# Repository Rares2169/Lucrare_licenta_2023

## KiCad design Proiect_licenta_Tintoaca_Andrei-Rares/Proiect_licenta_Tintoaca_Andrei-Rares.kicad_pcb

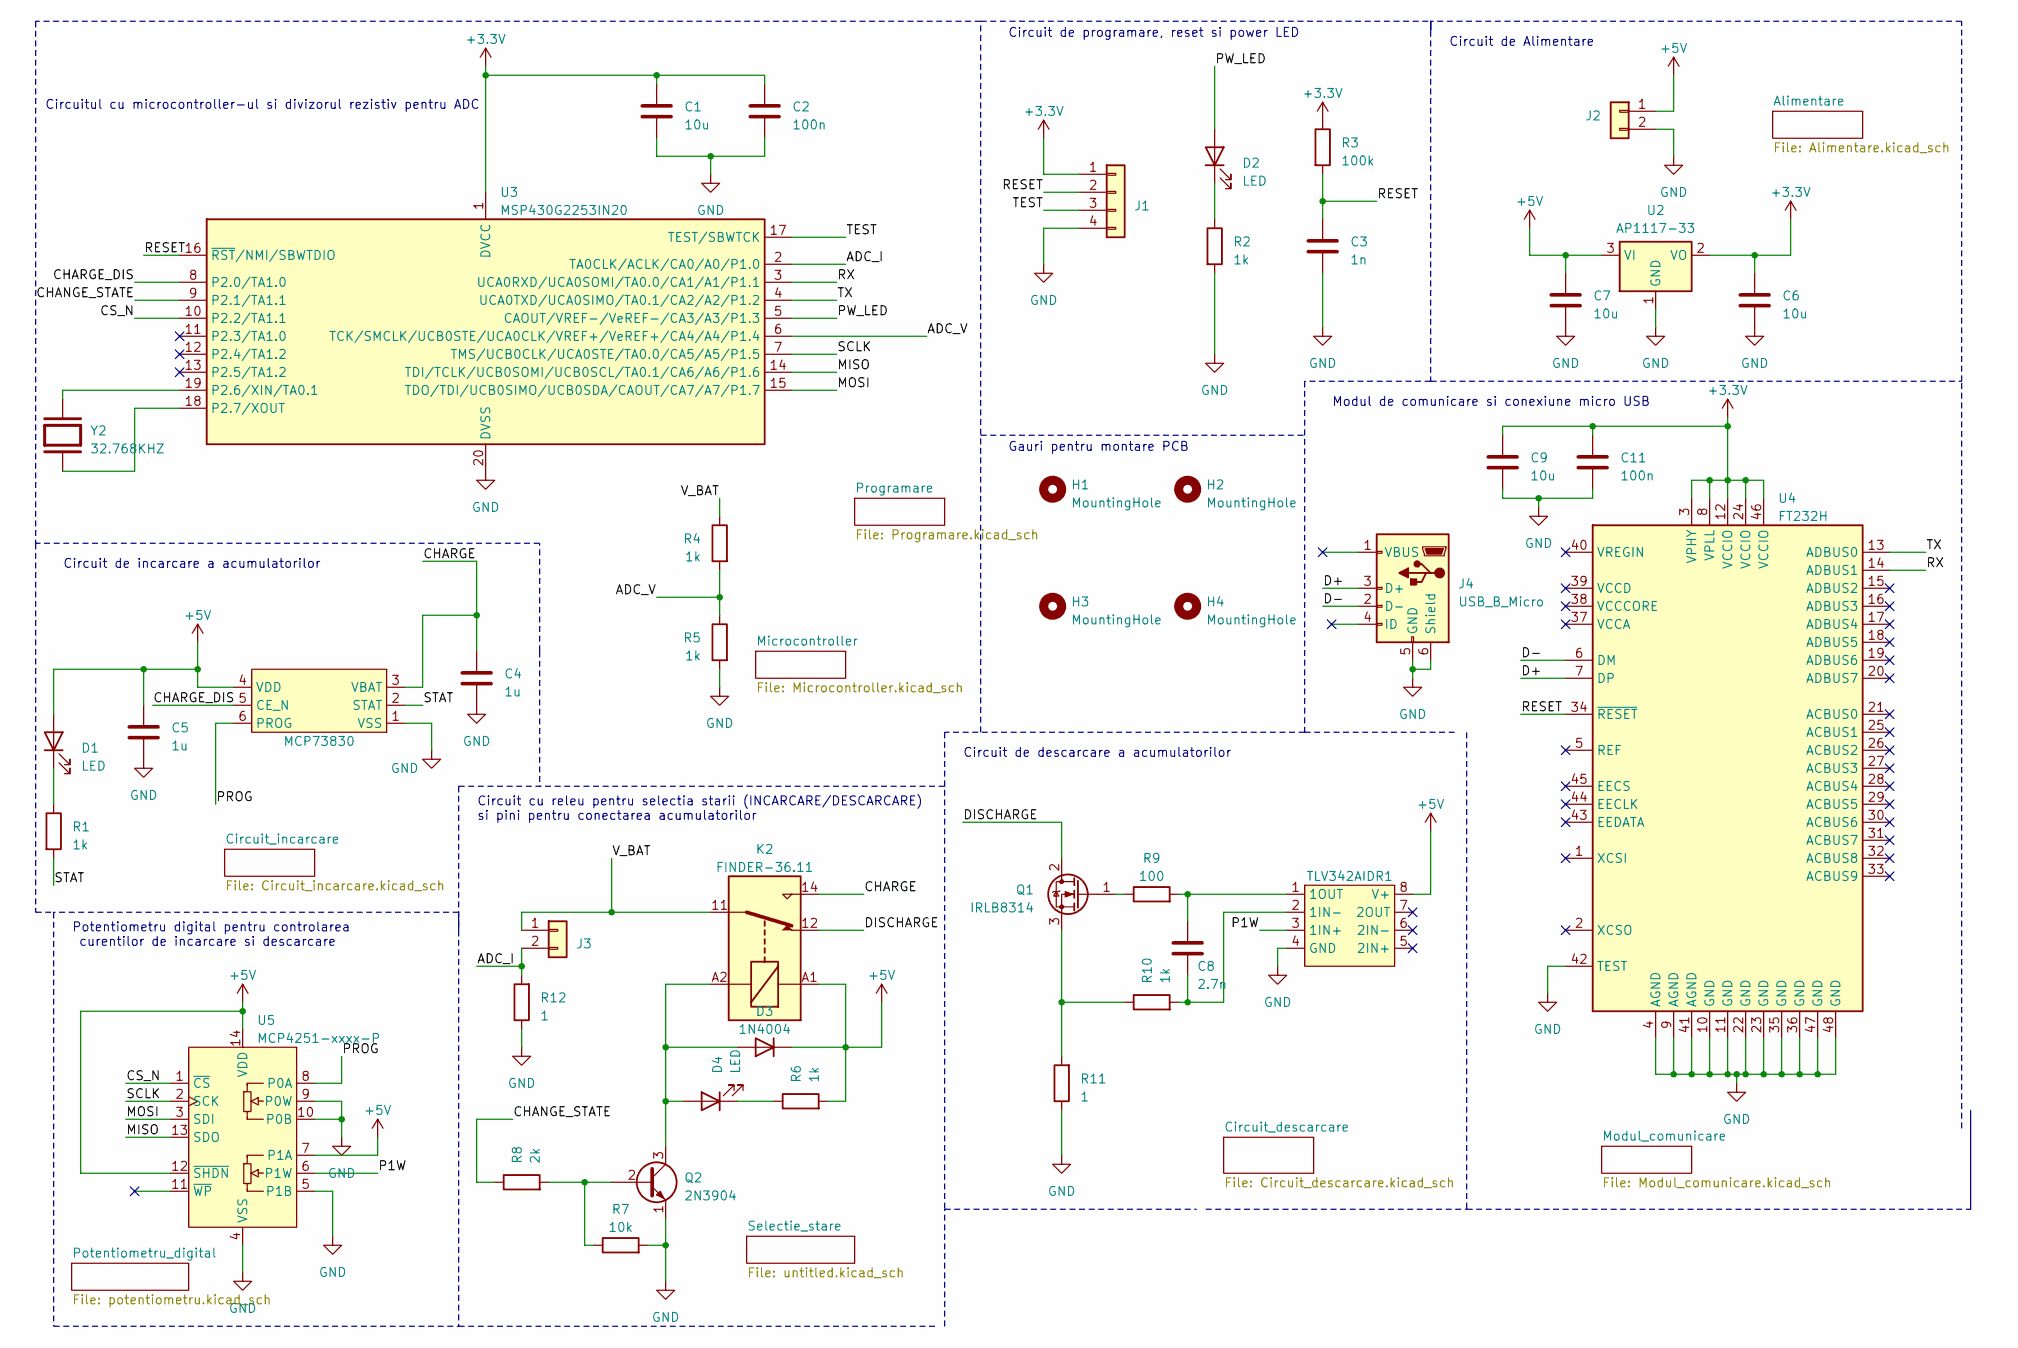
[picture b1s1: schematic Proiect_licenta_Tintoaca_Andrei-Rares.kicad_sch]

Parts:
C1, C6, C7, C9: 10u; C_1206_3216Metric
C2, C11: 100n; C_1206_3216Metric
C3: 1n; C_1206_3216Metric
C4, C5: 1u; C_1206_3216Metric
C8: 2.7n; C_1206_3216Metric
D1, D2, D4: LED; LED_1206_3216Metric
D3: 1N4004; D_1206_3216Metric
H1, H2, H3, H4: MountingHole; MountingHole_3.2mm_M3
J1: Conn_01x04; PinHeader_1x04_P2.00mm_Vertical
J2: Conn_01x02; PinHeader_1x02_P2.00mm_Vertical
J3: ACUMULATOR; PinHeader_1x02_P2.00mm_Vertical
J4: USB_B_Micro; USB_Micro-B_Molex-105017-0001
K2: FINDER-36.11; Relay_SPDT_Finder_36.11
MCP73830: TDFN-6-1EP_2.5x2.5mm_P0.65mm_EP1.3x2mm
Q1: IRLB8314; TO-220-3_Vertical
Q2: 2N3904; TO-92_Inline
R1, R2, R4, R5, R6, R10: 1k; R_1206_3216Metric
R3: 100k; R_1206_3216Metric
R7: 10k; R_1206_3216Metric
R8: 2k; R_1206_3216Metric
R9: 100; R_1206_3216Metric
R11, R12: 1; R_2512_6332Metric
TLV342AIDR1: SOIC-8-1EP_3.9x4.9mm_P1.27mm_EP2.29x3mm
U2: AP1117-33; SOT-223-3_TabPin2
U3: MSP430G2253IN20; DIP-20_W7.62mm
U4: FT232H; LQFP-48_7x7mm_P0.5mm
U5: MCP4251-xxxx-P; DIP-14_W7.62mm
Y2: 32.768KHZ; Crystal_AT310_D3.0mm_L10.0mm_Horizontal; PARTREV 08.19.15

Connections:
+3.3V: C1.1, C2.1, C6.1, C9.1, C11.1, J1.1, R3.1, U2.2 (VO), U3.1 (DVCC), U4.3 (VPHY), U4.8 (VPLL), U4.12 (VCCIO), U4.24 (VCCIO), U4.46 (VCCIO)
+5V: C5.1, C7.1, D1.2 (A), D3.1 (K), J2.1, K2.A1, MCP73830.4 (VDD), R6.2, TLV342AIDR1.8 (V+), U2.3 (VI), U5.7 (P1A), U5.12 (~SHDN), U5.14 (VDD)
/ADC_I: J3.2, R12.2, U3.2 (TA0CLK/ACLK/CA0/A0/P1.0)
/ADC_V: R4.2, R5.1, U3.6 (TCK/SMCLK/UCB0STE/UCA0CLK/VREF+/VeREF+/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)
/CHANGE_STATE: R8.1, U3.9 (P2.1/TA1.1)
/CHARGE: C4.1, K2.14, MCP73830.3 (VBAT)
/CHARGE_DIS: MCP73830.5 (CE_N), U3.8 (P2.0/TA1.0)
/CS_N: U3.10 (P2.2/TA1.1), U5.1 (~CS)
/D+: J4.3 (D+), U4.7 (DP)
/D-: J4.2 (D-), U4.6 (DM)
/DISCHARGE: K2.12, Q1.2 (D)
/MISO: U3.14 (TDI/TCLK/UCB0SOMI/UCB0SCL/TA0.1/CA6/A6/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), U5.13 (SDO)
/MOSI: U3.15 (TDO/TDI/UCB0SIMO/UCB0SDA/CAOUT/CA7/A7/P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), U5.3 (SDI)
/P1W: TLV342AIDR1.3 (1IN+), U5.6 (P1W)
/PROG: MCP73830.6 (PROG), U5.8 (P0A)
/PW_LED: D2.2 (A), U3.5 (CAOUT/VREF-/VeREF-/CA3/A3/P1.3)
/RESET: C3.1, J1.2, R3.2, U3.16 (~RST/NMI/SBWTDIO), U4.34 (~RESET)
/RX: U3.3 (UCA0RXD/UCA0SOMI/TA0.0/CA1/A1/P1.1), U4.14 (ADBUS1)
/SCLK: U3.7 (TMS/UCB0CLK/UCA0STE/TA0.0/CA5/A5/P1.5), U5.2 (SCK)
/STAT: MCP73830.2 (STAT), R1.2
/TEST: J1.3, U3.17 (TEST/SBWTCK)
/TX: U3.4 (UCA0TXD/UCA0SIMO/TA0.1/CA2/A2/P1.2), U4.13 (ADBUS0)
/V_BAT: J3.1, K2.11, R4.1
GND: C1.2, C2.2, C3.2, C4.2, C5.2, C6.2, C7.2, C9.2, C11.2, J1.4, J2.2, J4.5 (GND), J4.6 (Shield), MCP73830.1 (VSS), Q2.1 (E), R2.2, R5.2, R7.2, R11.1, R12.1, TLV342AIDR1.4 (GND), U2.1 (GND), U3.20 (DVSS), U4.4 (AGND), U4.9 (AGND), U4.10 (GND), U4.11 (GND), U4.22 (GND), U4.23 (GND), U4.35 (GND), U4.36 (GND), U4.41 (AGND), U4.42 (TEST), U4.47 (GND), U4.48 (GND), U5.4 (VSS), U5.5 (P1B), U5.9 (P0W), U5.10 (P0B)
unnamed: D1.1 (K), R1.1
unnamed: D2.1 (K), R2.1
unnamed: D3.2 (A), D4.2 (A), K2.A2, Q2.3 (C)
unnamed: D4.1 (K), R6.1
unnamed: Q1.1 (G), R9.1
unnamed: Q1.3 (S), R10.1, R11.2
unnamed: Q2.2 (B), R7.1, R8.2
unnamed: C8.2, R10.2, TLV342AIDR1.2 (1IN-)
unnamed: C8.1, R9.2, TLV342AIDR1.1 (1OUT)
unnamed: U3.19 (P2.6/XIN/TA0.1), Y2.2
unnamed: U3.18 (P2.7/XOUT), Y2.1

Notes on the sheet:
Modul de comunicare si conexiune micro USB
Circuit cu releu pentru selectia starii (INCARCARE/DESCARCARE) si pini pentru conectarea acumulatorilor
Circuitul cu microcontroller-ul si divizorul rezistiv pentru ADC
Circuit de Alimentare
Potentiometru digital pentru controlarea curentilor de incarcare si descarcare
Circuit de descarcare a acumulatorilor
Circuit de programare, reset si power LED
Circuit de incarcare a acumulatorilor
Gauri pentru montare PCB

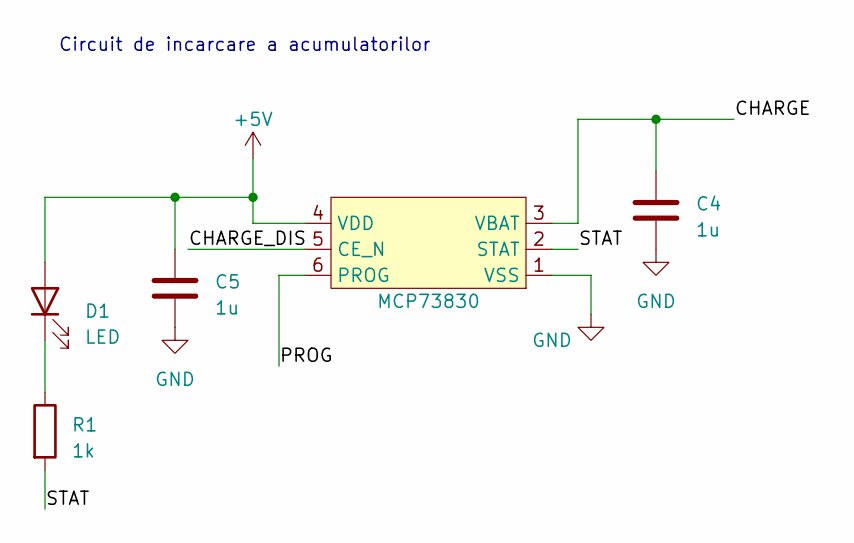
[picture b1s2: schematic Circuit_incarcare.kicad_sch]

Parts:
C4, C5: 1u; C_1206_3216Metric
D1: LED; LED_1206_3216Metric
MCP73830: TDFN-6-1EP_2.5x2.5mm_P0.65mm_EP1.3x2mm
R1: 1k; R_1206_3216Metric

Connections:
+5V: C5.1, D1.2 (A), MCP73830.4 (VDD); also elsewhere on the board
/CHARGE: C4.1, MCP73830.3 (VBAT); also elsewhere on the board
/CHARGE_DIS: MCP73830.5 (CE_N); also elsewhere on the board
/PROG: MCP73830.6 (PROG); also elsewhere on the board
/STAT: MCP73830.2 (STAT), R1.2
GND: C4.2, C5.2, MCP73830.1 (VSS); also elsewhere on the board
unnamed: D1.1 (K), R1.1

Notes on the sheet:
Circuit de incarcare a acumulatorilor

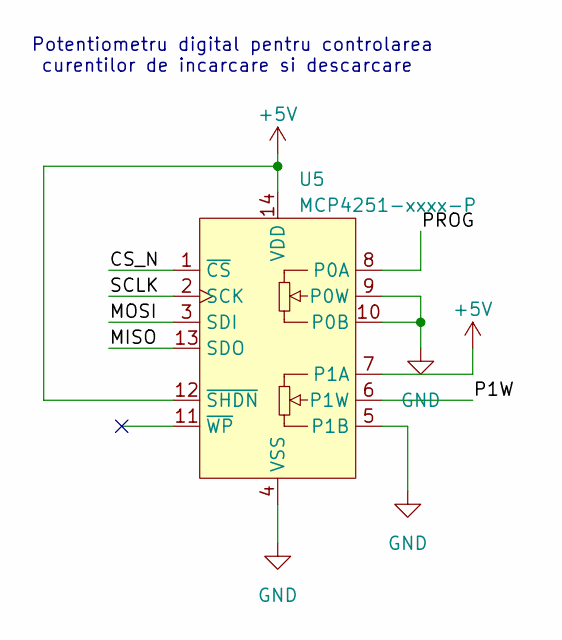
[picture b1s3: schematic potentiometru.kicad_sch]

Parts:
U5: MCP4251-xxxx-P; DIP-14_W7.62mm

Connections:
+5V: U5.7 (P1A), U5.12 (~SHDN), U5.14 (VDD); also elsewhere on the board
/CS_N: U5.1 (~CS); also elsewhere on the board
/MISO: U5.13 (SDO); also elsewhere on the board
/MOSI: U5.3 (SDI); also elsewhere on the board
/P1W: U5.6 (P1W); also elsewhere on the board
/PROG: U5.8 (P0A); also elsewhere on the board
/SCLK: U5.2 (SCK); also elsewhere on the board
GND: U5.4 (VSS), U5.5 (P1B), U5.9 (P0W), U5.10 (P0B); also elsewhere on the board

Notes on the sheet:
Potentiometru digital pentru controlarea curentilor de incarcare si descarcare

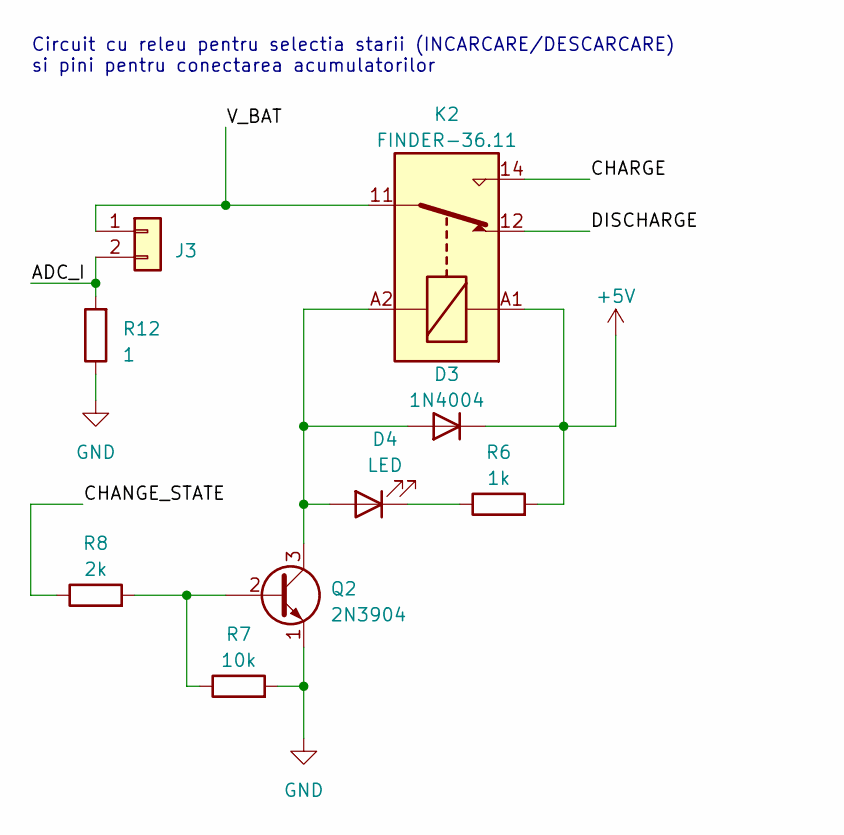
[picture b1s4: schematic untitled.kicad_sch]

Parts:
D3: 1N4004; D_1206_3216Metric
D4: LED; LED_1206_3216Metric
J3: ACUMULATOR; PinHeader_1x02_P2.00mm_Vertical
K2: FINDER-36.11; Relay_SPDT_Finder_36.11
Q2: 2N3904; TO-92_Inline
R6: 1k; R_1206_3216Metric
R7: 10k; R_1206_3216Metric
R8: 2k; R_1206_3216Metric
R12: 1; R_2512_6332Metric

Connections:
+5V: D3.1 (K), K2.A1, R6.2; also elsewhere on the board
/ADC_I: J3.2, R12.2; also elsewhere on the board
/CHANGE_STATE: R8.1; also elsewhere on the board
/CHARGE: K2.14; also elsewhere on the board
/DISCHARGE: K2.12; also elsewhere on the board
/V_BAT: J3.1, K2.11; also elsewhere on the board
GND: Q2.1 (E), R7.2, R12.1; also elsewhere on the board
unnamed: D3.2 (A), D4.2 (A), K2.A2, Q2.3 (C)
unnamed: D4.1 (K), R6.1
unnamed: Q2.2 (B), R7.1, R8.2

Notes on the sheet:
Circuit cu releu pentru selectia starii (INCARCARE/DESCARCARE) si pini pentru conectarea acumulatorilor

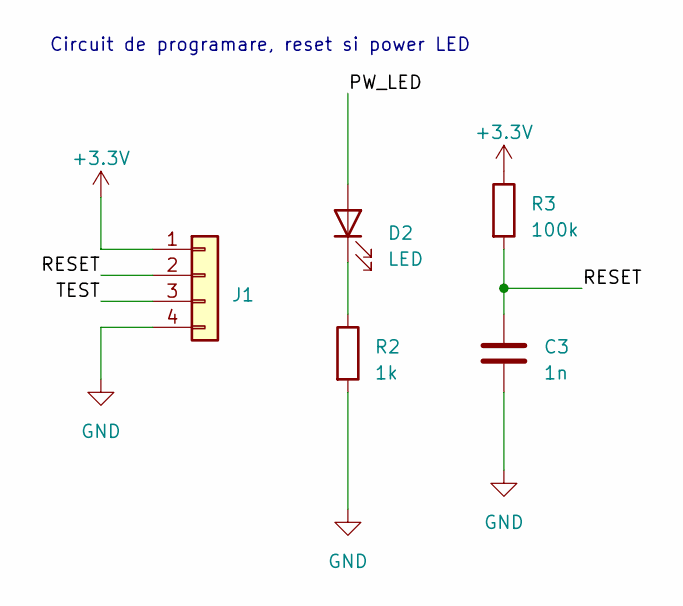
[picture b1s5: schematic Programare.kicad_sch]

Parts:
C3: 1n; C_1206_3216Metric
D2: LED; LED_1206_3216Metric
J1: Conn_01x04; PinHeader_1x04_P2.00mm_Vertical
R2: 1k; R_1206_3216Metric
R3: 100k; R_1206_3216Metric

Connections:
+3.3V: J1.1, R3.1; also elsewhere on the board
/PW_LED: D2.2 (A); also elsewhere on the board
/RESET: C3.1, J1.2, R3.2; also elsewhere on the board
/TEST: J1.3; also elsewhere on the board
GND: C3.2, J1.4, R2.2; also elsewhere on the board
unnamed: D2.1 (K), R2.1

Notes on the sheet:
Circuit de programare, reset si power LED

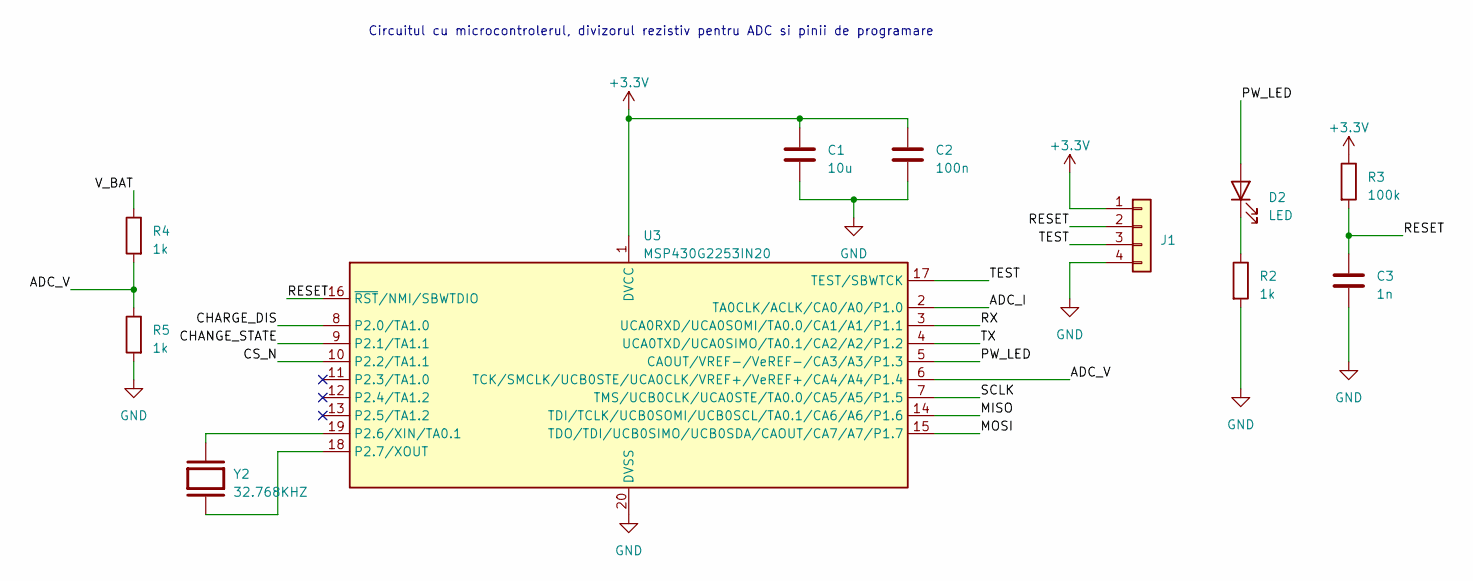
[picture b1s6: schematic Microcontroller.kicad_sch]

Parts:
C1: 10u; C_1206_3216Metric
C2: 100n; C_1206_3216Metric
C3: 1n; C_1206_3216Metric
D2: LED; LED_1206_3216Metric
J1: Conn_01x04; PinHeader_1x04_P2.00mm_Vertical
R2, R4, R5: 1k; R_1206_3216Metric
R3: 100k; R_1206_3216Metric
U3: MSP430G2253IN20; DIP-20_W7.62mm
Y2: 32.768KHZ; Crystal_AT310_D3.0mm_L10.0mm_Horizontal; PARTREV 08.19.15

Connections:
+3.3V: C1.1, C2.1, J1.1, R3.1, U3.1 (DVCC); also elsewhere on the board
/ADC_I: U3.2 (TA0CLK/ACLK/CA0/A0/P1.0); also elsewhere on the board
/ADC_V: R4.2, R5.1, U3.6 (TCK/SMCLK/UCB0STE/UCA0CLK/VREF+/VeREF+/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)
/CHANGE_STATE: U3.9 (P2.1/TA1.1); also elsewhere on the board
/CHARGE_DIS: U3.8 (P2.0/TA1.0); also elsewhere on the board
/CS_N: U3.10 (P2.2/TA1.1); also elsewhere on the board
/MISO: U3.14 (TDI/TCLK/UCB0SOMI/UCB0SCL/TA0.1/CA6/A6/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); also elsewhere on the board
/MOSI: U3.15 (TDO/TDI/UCB0SIMO/UCB0SDA/CAOUT/CA7/A7/P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); also elsewhere on the board
/PW_LED: D2.2 (A), U3.5 (CAOUT/VREF-/VeREF-/CA3/A3/P1.3)
/RESET: C3.1, J1.2, R3.2, U3.16 (~RST/NMI/SBWTDIO); also elsewhere on the board
/RX: U3.3 (UCA0RXD/UCA0SOMI/TA0.0/CA1/A1/P1.1); also elsewhere on the board
/SCLK: U3.7 (TMS/UCB0CLK/UCA0STE/TA0.0/CA5/A5/P1.5); also elsewhere on the board
/TEST: J1.3, U3.17 (TEST/SBWTCK)
/TX: U3.4 (UCA0TXD/UCA0SIMO/TA0.1/CA2/A2/P1.2); also elsewhere on the board
/V_BAT: R4.1; also elsewhere on the board
GND: C1.2, C2.2, C3.2, J1.4, R2.2, R5.2, U3.20 (DVSS); also elsewhere on the board
unnamed: D2.1 (K), R2.1
unnamed: U3.19 (P2.6/XIN/TA0.1), Y2.2
unnamed: U3.18 (P2.7/XOUT), Y2.1

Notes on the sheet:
Circuitul cu microcontrolerul, divizorul rezistiv pentru ADC si pinii de programare

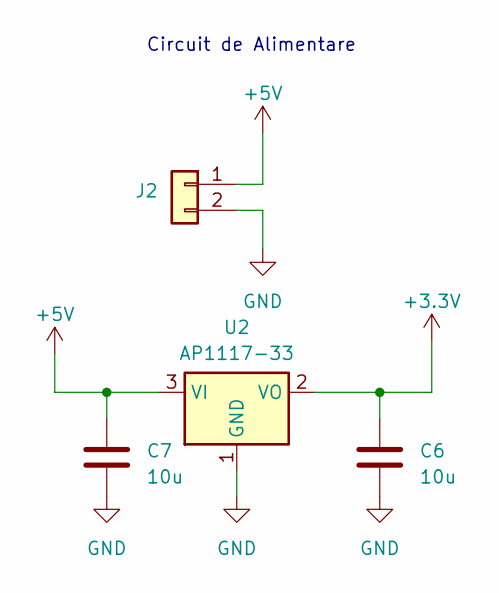
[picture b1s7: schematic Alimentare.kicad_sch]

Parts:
C6, C7: 10u; C_1206_3216Metric
J2: Conn_01x02; PinHeader_1x02_P2.00mm_Vertical
U2: AP1117-33; SOT-223-3_TabPin2

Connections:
+3.3V: C6.1, U2.2 (VO); also elsewhere on the board
+5V: C7.1, J2.1, U2.3 (VI); also elsewhere on the board
GND: C6.2, C7.2, J2.2, U2.1 (GND); also elsewhere on the board

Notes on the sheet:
Circuit de Alimentare

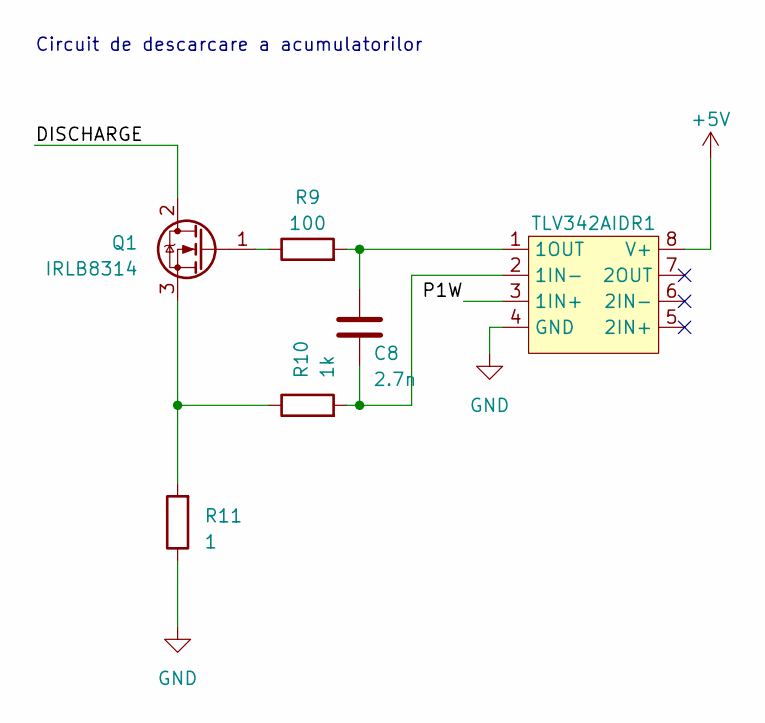
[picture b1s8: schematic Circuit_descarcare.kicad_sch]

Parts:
C8: 2.7n; C_1206_3216Metric
Q1: IRLB8314; TO-220-3_Vertical
R9: 100; R_1206_3216Metric
R10: 1k; R_1206_3216Metric
R11: 1; R_2512_6332Metric
TLV342AIDR1: SOIC-8-1EP_3.9x4.9mm_P1.27mm_EP2.29x3mm

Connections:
+5V: TLV342AIDR1.8 (V+); also elsewhere on the board
/DISCHARGE: Q1.2 (D); also elsewhere on the board
/P1W: TLV342AIDR1.3 (1IN+); also elsewhere on the board
GND: R11.1, TLV342AIDR1.4 (GND); also elsewhere on the board
unnamed: Q1.1 (G), R9.1
unnamed: Q1.3 (S), R10.1, R11.2
unnamed: C8.2, R10.2, TLV342AIDR1.2 (1IN-)
unnamed: C8.1, R9.2, TLV342AIDR1.1 (1OUT)

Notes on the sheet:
Circuit de descarcare a acumulatorilor

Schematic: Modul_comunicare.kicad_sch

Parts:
C9: 10u; C_1206_3216Metric
C11: 100n; C_1206_3216Metric
J4: USB_B_Micro; USB_Micro-B_Molex-105017-0001
U4: FT232H; LQFP-48_7x7mm_P0.5mm

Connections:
+3.3V: C9.1, C11.1, U4.3 (VPHY), U4.8 (VPLL), U4.12 (VCCIO), U4.24 (VCCIO), U4.46 (VCCIO); also elsewhere on the board
/D+: J4.3 (D+), U4.7 (DP)
/D-: J4.2 (D-), U4.6 (DM)
/RESET: U4.34 (~RESET); also elsewhere on the board
/RX: U4.14 (ADBUS1); also elsewhere on the board
/TX: U4.13 (ADBUS0); also elsewhere on the board
GND: C9.2, C11.2, J4.5 (GND), J4.6 (Shield), U4.4 (AGND), U4.9 (AGND), U4.10 (GND), U4.11 (GND), U4.22 (GND), U4.23 (GND), U4.35 (GND), U4.36 (GND), U4.41 (AGND), U4.42 (TEST), U4.47 (GND), U4.48 (GND); also elsewhere on the board

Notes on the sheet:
Modul de comunicare si conexiune micro USB

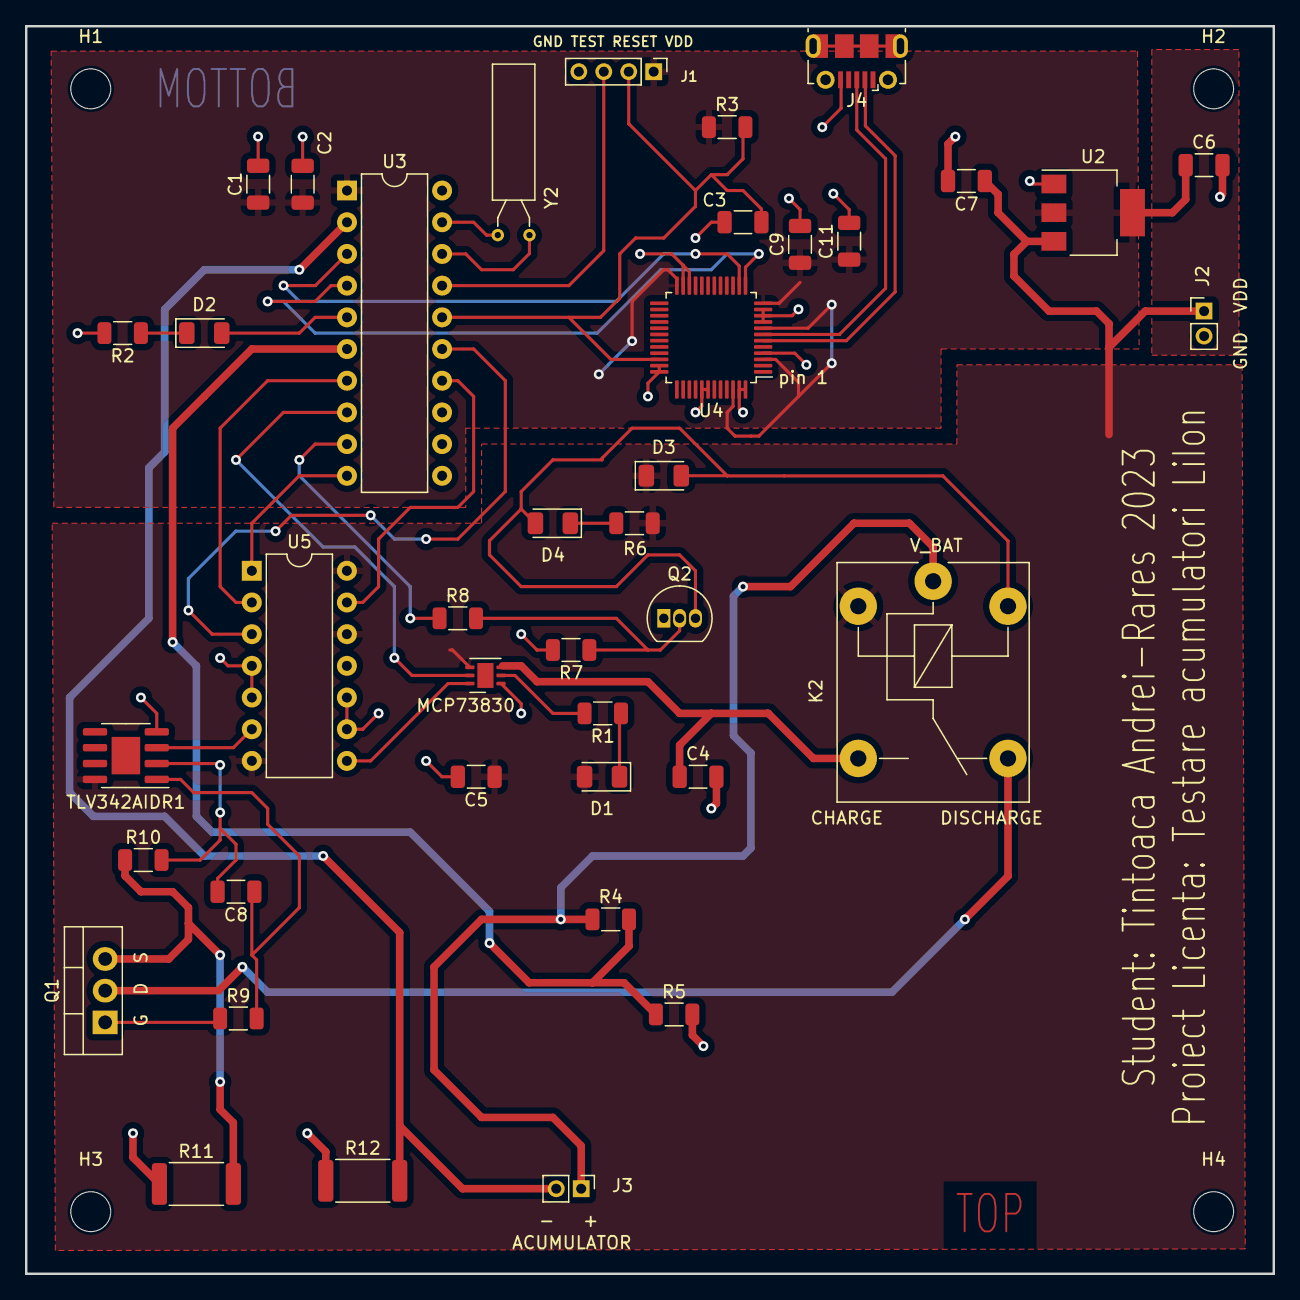
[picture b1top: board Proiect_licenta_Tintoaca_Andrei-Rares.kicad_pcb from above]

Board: 2 copper layers, 100.0 x 100.0 mm, 44 parts (0 on the bottom side), 35 nets.

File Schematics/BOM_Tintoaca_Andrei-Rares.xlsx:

Reference(s) | Status | CANTITATE | Value | Footprint | Pret total
C1, C6, C7, C9 |  | 4 | 10u | C_1206_3220 | ?
C2, C11 |  | 2 | 100n | C_1206_3220 | ?
C3 |  | 1 | 1n | C_1206_3220 | ?
C4, C5 |  | 2 | 1u | C_1206_3220 | ?
C8 |  | 1 | 2.7n | C_1206_3220 | ?
D1, D2, D4 |  | 3 | LED | LED_1206_3216 | ?
D3 |  | 1 | 1N4004 | D_1206_3216 | ?
J1 |  | 1 | Conn_01x04 | Connector_PinHeader_2.00mm:PinHeader_1x04_P2.00mm_Vertical | -
J2 |  | 1 | Conn_01x02 | Connector_PinHeader_2.00mm:PinHeader_1x02_P2.00mm_Vertical | -
J3 |  | 1 | Conn_01x02 | Connector_PinHeader_2.00mm:PinHeader_1x02_P2.00mm_Vertical | -
J4 |  | 1 | USB_B_Micro | USB_Micro-B_Molex-105017-0001 | -
K1 | primit | 1 | G5Q-1 | Relay_THT:Relay_SPDT_Omron-G5Q-1 | -
MCP73830 | primit x2 | 2 | MCP73830 | TDFN-6-1EP_2.5x2.5mm_P0.65mm_EP1.3x2mm | 12 lei
Q1 | comandat x2 | 2 | IRLB8314 | TO-220-3_Vertical | 10 lei
Q2 |  | 1 | 2N3904 | TO-92_Inline | -
R1, R2, R4, R5, R6, R10 |  | 6 | 1k | R_1206_3220 | ?
R3 |  | 1 | 100k | R_1206_3220 | ?
R7 |  | 1 | 10k | R_1206_3220 | ?
R8 |  | 1 | 2k | R_1206_3220 | ?
R9 |  | 1 | 100 | R_1206_3220 | ?
R11, R12 |  | 4 | 1 | R_2512_6332 | 4 lei
TLV342AIDR1 | comandat x2 | 2 | ~ | SOIC-8 | 10 lei
U2 |  | 1 | AP1117-33 | SOT-223-3 | -
U3 |  | 1 | MSP430G2253IN20 | DIP-20 | 12 lei
U4 | comandat | 1 | FT232HL | LQFP-48 | 19 lei
U5 | primit x2 | 2 | MCP4251 | DIP-14 | 13 lei
Y2 |  | 1 | Crystal -32.768KHZ | Crystal_AT310_D3.0mm_L10.0mm_Horizontal | -
 |  |  |  |  | TOTAL DE PLATA: 70-80 lei

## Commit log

2023-07-06 schematic
2023-07-06 schematics
2023-07-06 main.c
2023-07-06 main
